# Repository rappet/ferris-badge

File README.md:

# Ferris STM32L0 badge

Small badge running on a coin cell using a STM32L031G6U with embassy.

## Known bugs

- BOOT0 is not connected
- Reverse polarity protection diode should be swapped with MOSFET
- Output caps could be larger to minimize peak current during PWM
- Shutdown microcontroller with external MOSFET
  - Current power consumption when turned off was measured at ~16µF

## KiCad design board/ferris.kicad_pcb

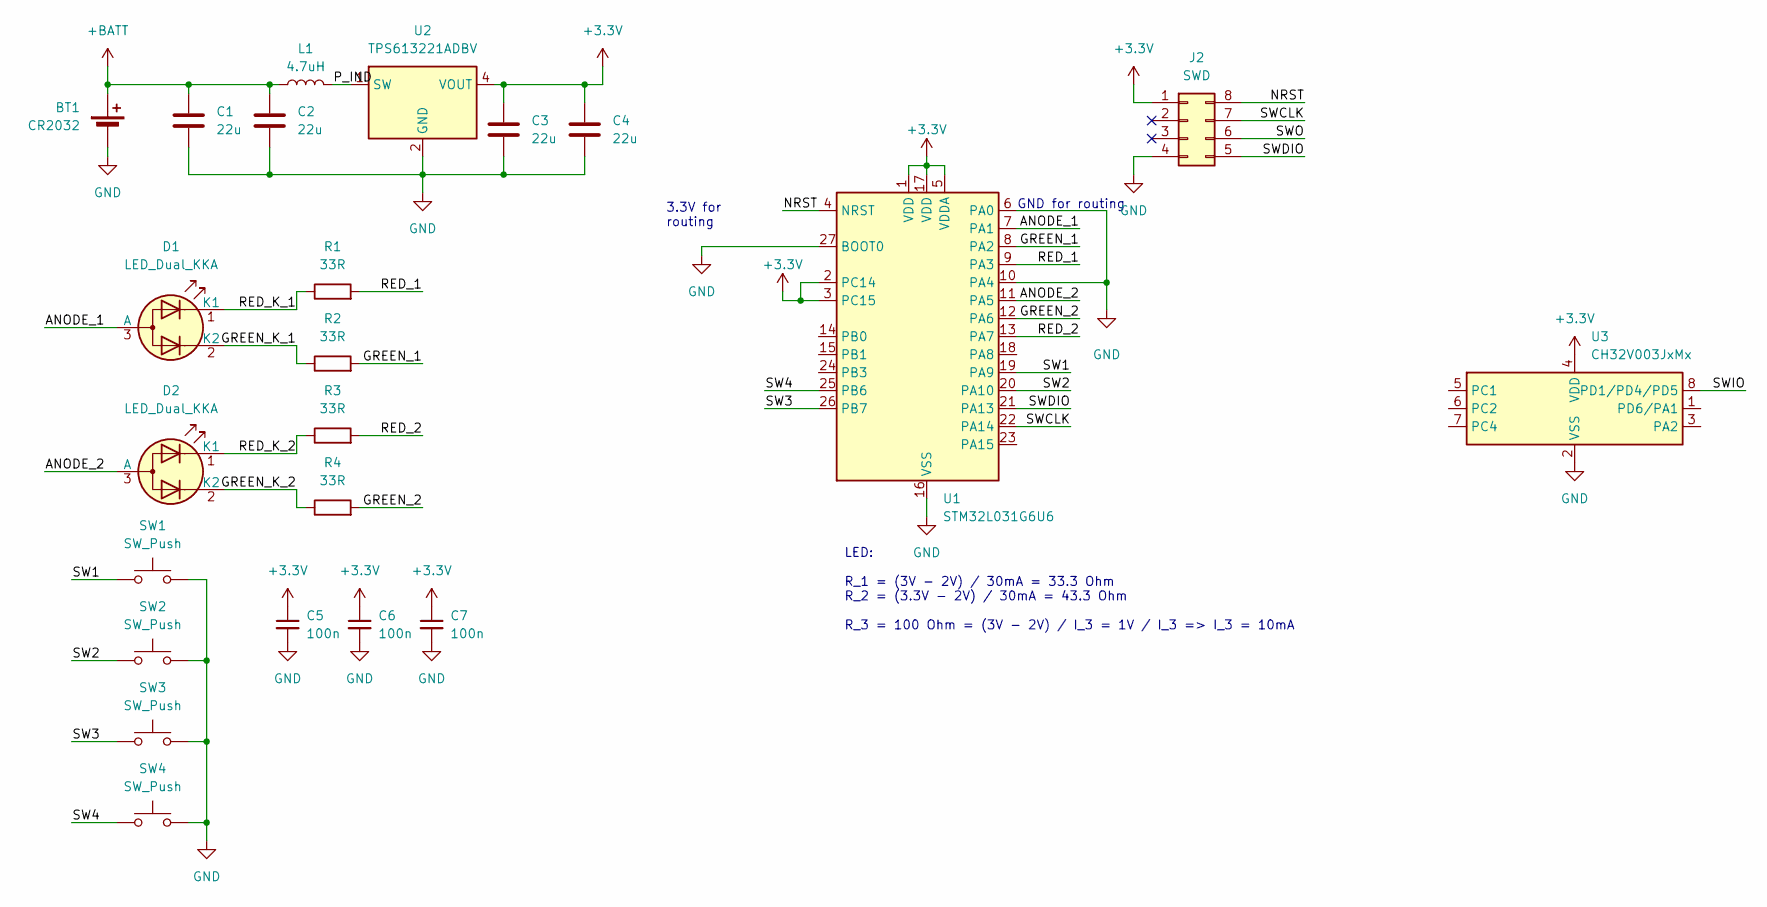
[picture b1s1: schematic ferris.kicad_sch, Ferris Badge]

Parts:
BT1: CR2032; BatteryHolder_Keystone_3034_1x20mm; LCSC C964833
C1, C2, C3, C4: 22u; C_0805_2012Metric_Pad1.18x1.45mm_HandSolder
C5, C6, C7: 100n; C_0402_1005Metric
D1, D2: LED_Dual_KKA; LED_LiteOn_LTST-S326
J2: SWD; SOIC_clipProgSmall
L1: 4.7uH; L_1008_2520Metric_Pad1.43x2.20mm_HandSolder
R1, R2, R3, R4: 33R; R_0402_1005Metric
SW1, SW2, SW3, SW4: SW_Push; SW_Push_1P1T_XKB_TS-1187A
U1: STM32L031G6U6; QFN-28_4x4mm_P0.5mm
U2: TPS613221ADBV; SOT-23-5_HandSoldering
U3: CH32V003JxMx; SOP-8_3.9x4.9mm_P1.27mm

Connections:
+3.3V: C3.1, C4.1, C5.1, C6.1, C7.1, J2.1, U1.1 (VDD), U1.2 (PC14), U1.3 (PC15), U1.5 (VDDA), U1.17 (VDD), U2.4 (VOUT), U3.4 (VDD)
+BATT: BT1.1 (+), C1.1, C2.1, L1.1
/ANODE_1: D1.3 (A), U1.7 (PA1)
/ANODE_2: D2.3 (A), U1.11 (PA5)
/GREEN_1: R2.2, U1.8 (PA2)
/GREEN_2: R4.2, U1.12 (PA6)
/GREEN_K_1: D1.2 (K2), R2.1
/GREEN_K_2: D2.2 (K2), R4.1
/NRST: J2.8, U1.4 (NRST)
/P_IND: L1.2, U2.1 (SW)
/RED_1: R1.2, U1.9 (PA3)
/RED_2: R3.2, U1.13 (PA7)
/RED_K_1: D1.1 (K1), R1.1
/RED_K_2: D2.1 (K1), R3.1
/SW1: SW1.1, U1.19 (PA9)
/SW2: SW2.1, U1.20 (PA10)
/SW3: SW3.1, U1.26 (PB7)
/SW4: SW4.1, U1.25 (PB6)
/SWCLK: J2.7, U1.22 (PA14)
/SWDIO: J2.5, U1.21 (PA13)
/SWIO: U3.8 (PD1/PD4/PD5)
/SWO: J2.6
GND: BT1.2 (-), C1.2, C2.2, C3.2, C4.2, C5.2, C6.2, C7.2, J2.4, SW1.2, SW2.2, SW3.2, SW4.2, U1.6 (PA0), U1.10 (PA4), U1.16 (VSS), U1.27 (BOOT0), U1.28 (VSS), U2.2 (GND), U3.2 (VSS)

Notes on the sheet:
3.3V for routing
LED: R_1 = (3V - 2V) / 30mA = 33.3 Ohm R_2 = (3.3V - 2V) / 30mA = 43.3 Ohm R_3 = 100 Ohm = (3V - 2V) / I_3 = 1V / I_3 => I_3 = 10mA
GND for routing

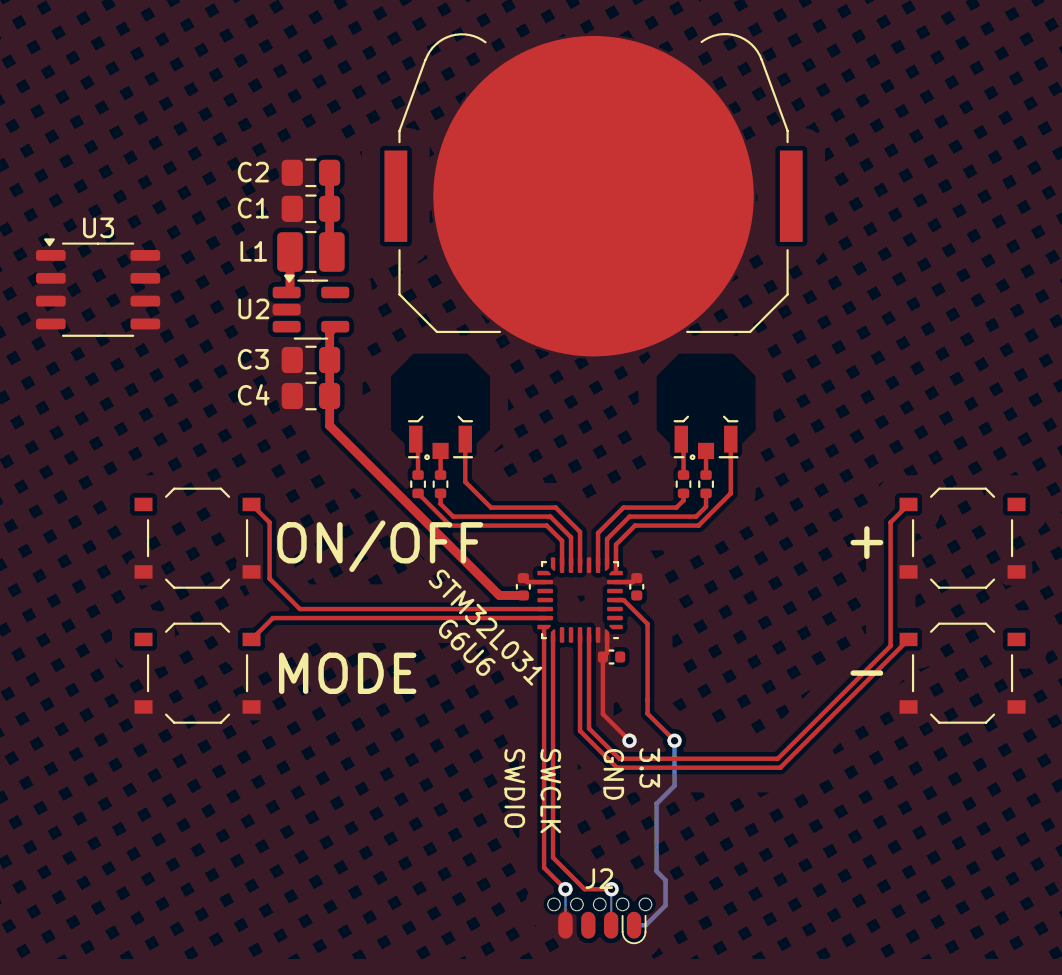
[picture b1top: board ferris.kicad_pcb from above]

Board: 2 copper layers, 23 parts (0 on the bottom side), 21 nets.

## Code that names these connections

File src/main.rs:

#![no_std]
#![no_main]

mod button;
mod eye;

use defmt::*;
use defmt_rtt as _;
use embassy_executor::Spawner;
use embassy_stm32::{
    exti::ExtiInput,
    gpio::{Input, Level, Output, OutputType, Pull, Speed},
    low_power::{stop_ready, Executor, StopMode},
    peripherals::{IWDG, TIM21, TIM22},
    rcc::{self, MSIRange, VoltageScale},
    rtc::{Rtc, RtcConfig},
    time::Hertz,
    timer::{
        low_level::CountingMode,
        simple_pwm::{PwmPin, SimplePwm, SimplePwmChannel},
    },
    wdg::IndependentWatchdog,
    Config,
};
use embassy_time::{Instant, Timer};
use panic_halt as _;
use static_cell::StaticCell;

use crate::{button::Button, eye::Eye};

#[cortex_m_rt::entry]
fn main() -> ! {
    Executor::take().run(|spawner| {
        spawner.spawn(async_main(spawner)).unwrap();
    });
}

#[embassy_executor::task]
async fn async_main(_spawner: Spawner) {
    let p = embassy_stm32::init({
        let mut config = Config::default();
        config.rcc = rcc::Config {
            msi: Some(MSIRange::RANGE4M),
            voltage_scale: VoltageScale::RANGE1,
            ..rcc::Config::default()
        };
        config.enable_debug_during_sleep = false;
        config
    });

    let rtc = Rtc::new(p.RTC, RtcConfig::default());
    static RTC: StaticCell<Rtc> = StaticCell::new();
    let rtc = RTC.init(rtc);
    embassy_stm32::low_power::stop_with_rtc(rtc);

    info!("Started 🦀");

    let mut btn_on = ExtiInput::new(p.PA9, p.EXTI9, Pull::Up);

    info!("Waiting for on!");
    info!("Low power mode enabled: {}", stop_ready(StopMode::Stop2));

    btn_on.wait_for_low().await;

    let mut good_boy = IndependentWatchdog::new(p.IWDG, 1_000 * 1_000 * 3);
    good_boy.unleash();

    good_boy.pet();

    info!("On!");

    let _anode_1 = Output::new(p.PA1, Level::High, Speed::Low);
    let _anode_2 = Output::new(p.PA5, Level::High, Speed::Low);

    let mut peripherals = {
        Timer::after_millis(1).await;

        let btn_on = Button::new(btn_on);
        let btn_mode = Button::new(Input::new(p.PA10, Pull::Up));

        let green_1 = PwmPin::new_ch1(p.PA2, OutputType::PushPull);
        let red_1 = PwmPin::new_ch2(p.PA3, OutputType::PushPull);
        let mut pwm_1 = SimplePwm::new(
            p.TIM21,
            Some(green_1),
            Some(red_1),
            None,
            None,
            Hertz::hz(500),
            CountingMode::EdgeAlignedUp,
        )
        .split();
        pwm_1.ch1.enable();
        pwm_1.ch2.enable();

        let eye_left = Eye::new(pwm_1.ch1, pwm_1.ch2);

        let green_2 = PwmPin::new_ch1(p.PA6, OutputType::PushPull);
        let red_2 = PwmPin::new_ch2(p.PA7, OutputType::PushPull);
        let mut pwm_2 = SimplePwm::new(
            p.TIM22,
            Some(green_2),
            Some(red_2),
            None,
            None,
            Hertz::hz(500),
            CountingMode::default(),
        )
        .split();
        pwm_2.ch1.enable();
        pwm_2.ch2.enable();

        let eye_right = Eye::new(pwm_2.ch1, pwm_2.ch2);

        BadgePeripherals {
            eye_left,
            eye_right,
            btn_on,
            btn_mode,
            good_boy,
        }
    };

    let mut mode = Mode::Red;

    loop {
        info!("Activated");

        active_loop(&mut peripherals, &mut mode).await;

        peripherals.eye_left.set_off();
        peripherals.eye_right.set_off();

        while !peripherals.btn_on.is_activated() {
            Timer::after_millis(10).await;
        }
    }
}

async fn active_loop(p: &mut BadgePeripherals<'_>, mode: &mut Mode) {
    let max_value = p.eye_left.max_value();
    info!("{}", max_value);

    while !p.btn_on.is_activated() {
        if p.btn_mode.is_activated() {
            mode.next();
        }
        match *mode {
            Mode::Red => {
                p.eye_left.set_red();
                p.eye_right.set_red();
            }
            Mode::Green => {
                p.eye_left.set_green();
                p.eye_right.set_green();
            }
            Mode::Yellow => {
                p.eye_left.set_value(max_value, max_value);
                p.eye_right.set_value(max_value, max_value);
            }
            Mode::Blink => {
                let now = Instant::now();
                if now.as_millis() % 1000 < 500 {
                    p.eye_left.set_red();
                    p.eye_right.set_green();
                } else {
                    p.eye_left.set_green();
                    p.eye_right.set_red();
                }
            }
            Mode::Fade => {
                let millis = (Instant::now().as_millis() % 4000) as u32;
                let fade = ((millis % 2000) * (max_value as u32) / 2000) as u16;
                if millis < 2000 {
                    p.eye_left.set_value(fade, max_value - fade);
                    p.eye_right.set_value(fade, max_value - fade);
                } else {
                    p.eye_left.set_value(max_value - fade, fade);
                    p.eye_right.set_value(max_value - fade, fade);
                }
            }
        }

        p.good_boy.pet();
        Timer::after_millis(1).await;
    }
    info!("Deactivated")
}

pub struct BadgePeripherals<'d> {
    pub eye_left: Eye<SimplePwmChannel<'d, TIM21>, SimplePwmChannel<'d, TIM21>>,
    pub eye_right: Eye<SimplePwmChannel<'d, TIM22>, SimplePwmChannel<'d, TIM22>>,
    pub btn_on: Button<ExtiInput<'d>>,
    pub btn_mode: Button<Input<'d>>,
    pub good_boy: IndependentWatchdog<'d, IWDG>,
}

pub enum Mode {
    Red,
    Green,
    Yellow,
    Blink,
    Fade,
}

impl Mode {
    pub fn next(&mut self) {
        *self = match *self {
            Mode::Red => Mode::Green,
            Mode::Green => Mode::Yellow,
            Mode::Yellow => Mode::Blink,
            Mode::Blink => Mode::Fade,
            Mode::Fade => Mode::Red,
        }
    }
}

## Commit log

2024-01-15 WIP firmware
2025-02-06 Add .rustfmt.toml
2025-02-06 Update everything and tidy up
2025-02-06 pwm: Use more abstractions
2025-02-06 Remove panic-probe with panic-halt
    This shrinks the code size so much, that the firmware fits into a 16kb
    flash.
2025-02-06 defmt: Set log level to error
2025-02-13 Switch from probe-run to probe-rs run
2025-02-13 Format Cargo.toml
2025-02-13 Enable debug symbols for elf file
2025-02-13 Fix low power mode
2025-02-13 Increase LED PWM frequency by a large margin
2025-02-13 Disable debug during deep sleep
2025-02-13 Move firmware to subfolder
2025-02-13 Add hardware
2025-02-13 fixup! Move firmware to subfolder
2025-02-13 Add README.md
2025-02-13 Update known bugs
